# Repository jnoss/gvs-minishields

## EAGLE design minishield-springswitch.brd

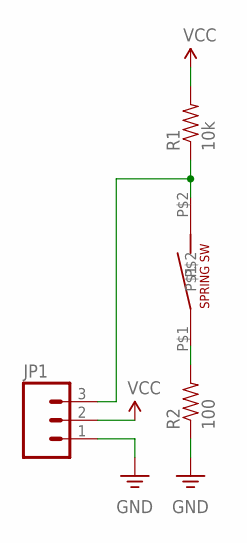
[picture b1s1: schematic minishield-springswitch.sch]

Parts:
JP1: M03PTH; 1X03
R1: 10k; 0402-RES
R2: 100; 0402-RES
S1: SPRING_SWITCH; SW-18020P-RA

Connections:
GND: JP1.1, R2.1
unnamed: JP1.3, R1.1, S1.P$2
unnamed: R2.2, S1.P$1
VCC: JP1.2, R1.2

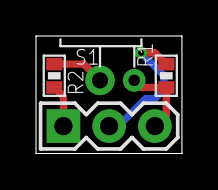
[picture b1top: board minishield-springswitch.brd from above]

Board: 2 copper layers, 8.1 x 6.5 mm, 4 parts (0 on the bottom side), 4 nets.

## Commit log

2016-09-01 initial commit: gitignore and eagle preview hook
2016-09-01 add button minishield
2016-09-02 add spring switch minishield

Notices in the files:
parts and their libraries:
SparkFun-Connectors: Licensing: CC v3.0 Share-Alike You are welcome to use this library for commercial purposes.
